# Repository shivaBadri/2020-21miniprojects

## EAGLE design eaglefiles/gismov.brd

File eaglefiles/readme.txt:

This folder contains Eagle Schematic and Board files

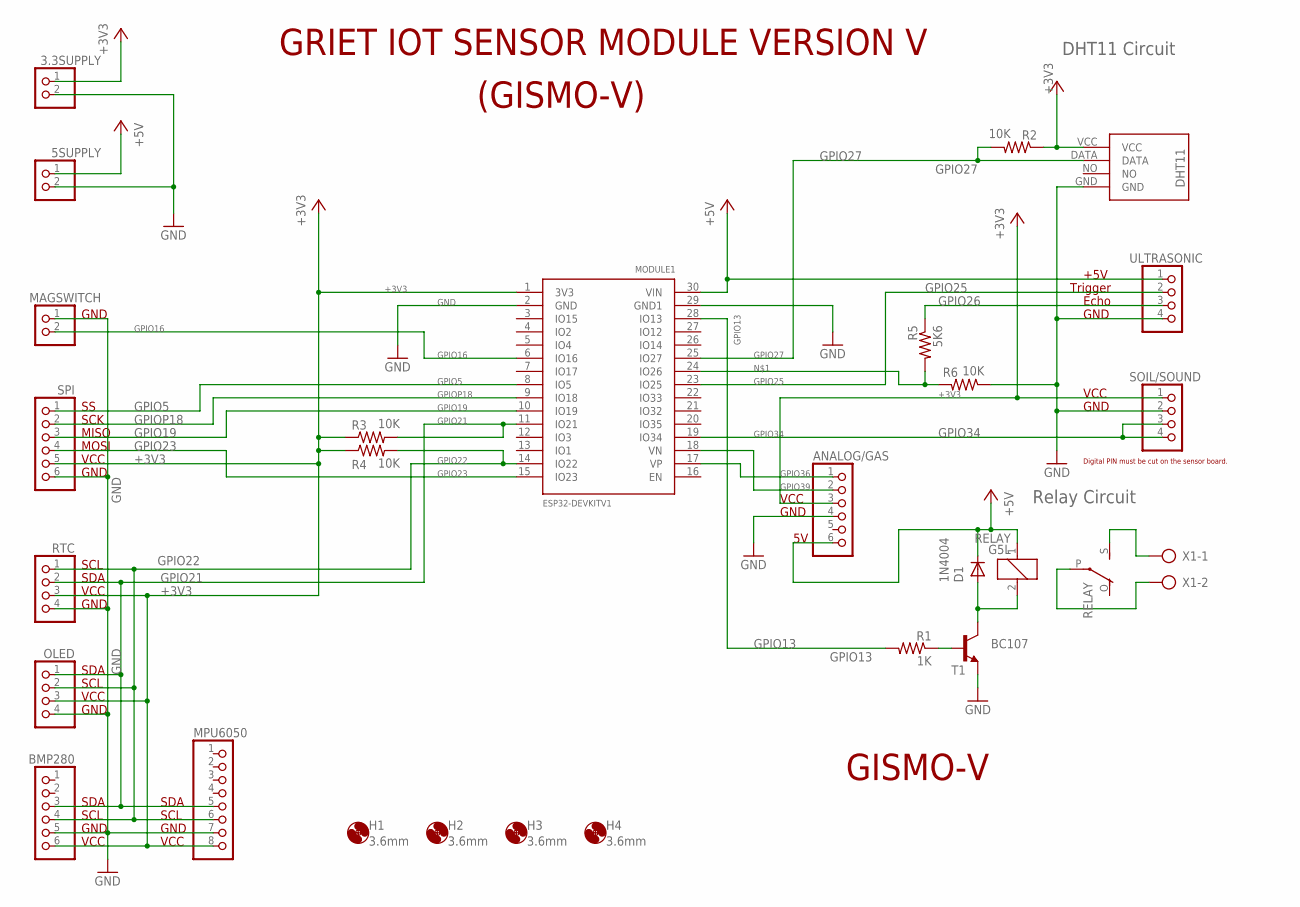
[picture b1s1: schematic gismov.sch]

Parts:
3.3SUPPLY, 5SUPPLY: PINHD-1X2; 1X02
ANALOG/GAS: PINHD-1X6; 1X06
BMP280: PINHD-1X6; 1X06
D1: 1N4004; DO41-10
H1, H2, H3, H4: 3.6mm; 3,6
MAGSWITCH: PINHD-1X2; 1X02
MODULE1: ESP32DEVKITV1; ESP32-DEVKITV1
MPU6050: PINHD-1X8; 1X08
OLED: PINHD-1X4; 1X04
R1: 1K; 0204/7
R2, R3, R4, R6: 10K; 0204/7
R5: 5K6; 0204/7
RELAY: G5L; G5LE
RTC: PINHD-1X4; 1X04
SOIL/SOUND: PINHD-1X4; 1X04
SPI: PINHD-1X6; 1X06
T1: BC107; TO18
U$2: DHT11
ULTRASONIC: PINHD-1X4; 1X04
X1: AK500/2

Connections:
+3V3: 3.3SUPPLY.1, ANALOG/GAS.3, BMP280.6, MODULE1.1 (3V3), MPU6050.8, OLED.3, R2.1, R3.1, R4.1, RTC.3, SOIL/SOUND.1, SPI.5, U$2.VCC
+5V: 5SUPPLY.1, ANALOG/GAS.6, D1.C, MODULE1.30 (VIN), RELAY.1, ULTRASONIC.1
GND: 3.3SUPPLY.2, 5SUPPLY.2, ANALOG/GAS.4, BMP280.5, MAGSWITCH.1, MODULE1.2 (GND), MODULE1.29 (GND1), MPU6050.7, OLED.4, R6.1, RTC.4, SOIL/SOUND.2, SPI.6, T1.1 (E), U$2.GND, ULTRASONIC.4
GPIO5: MODULE1.8 (IO5), SPI.1
GPIO13: MODULE1.28 (IO13), R1.2
GPIO16: MAGSWITCH.2, MODULE1.6 (IO16)
GPIO19: MODULE1.10 (IO19), SPI.3
GPIO21: BMP280.3, MODULE1.11 (IO21), MPU6050.5, OLED.1, R3.2, RTC.2
GPIO22: BMP280.4, MODULE1.14 (IO22), MPU6050.6, OLED.2, R4.2, RTC.1
GPIO23: MODULE1.15 (IO23), SPI.4
GPIO25: MODULE1.23 (IO25), ULTRASONIC.2
GPIO26: R5.1, ULTRASONIC.3
GPIO27: MODULE1.25 (IO27), R2.2, U$2.DATA
GPIO34: MODULE1.19 (IO34), SOIL/SOUND.3, SOIL/SOUND.4
GPIO36: ANALOG/GAS.1, MODULE1.17 (VP)
GPIO39: ANALOG/GAS.2, MODULE1.18 (VN)
GPIOP18: MODULE1.9 (IO18), SPI.2
unnamed: MODULE1.24 (IO26), R5.2, R6.2
unnamed: D1.A, RELAY.2, T1.3 (C)
unnamed: RELAY.P, X1.2
unnamed: RELAY.S, X1.1
unnamed: R1.1, T1.2 (B)

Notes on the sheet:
GISMO-V
DHT11 Circuit
Relay Circuit
GRIET IOT SENSOR MODULE VERSION V
(GISMO-V)
VCC
GND
SCL
SDA
SCK
MISO
MOSI
+5V
Trigger
Echo
Digital PIN must be cut on the sensor board.

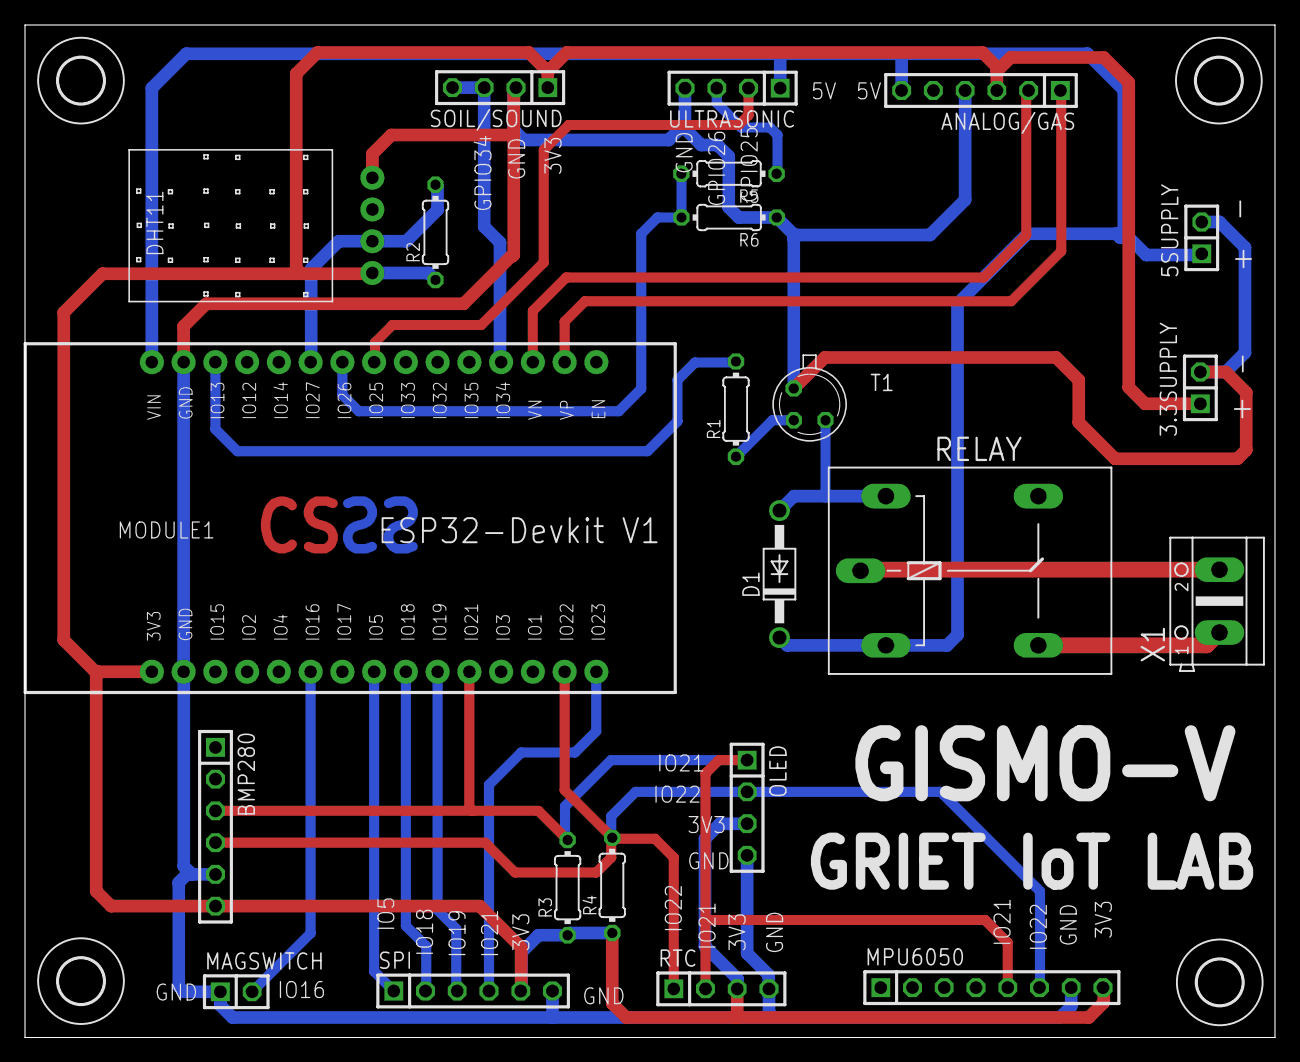
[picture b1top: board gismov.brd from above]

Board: 2 copper layers, 100.0 x 81.0 mm, 27 parts (0 on the bottom side), 22 nets.
